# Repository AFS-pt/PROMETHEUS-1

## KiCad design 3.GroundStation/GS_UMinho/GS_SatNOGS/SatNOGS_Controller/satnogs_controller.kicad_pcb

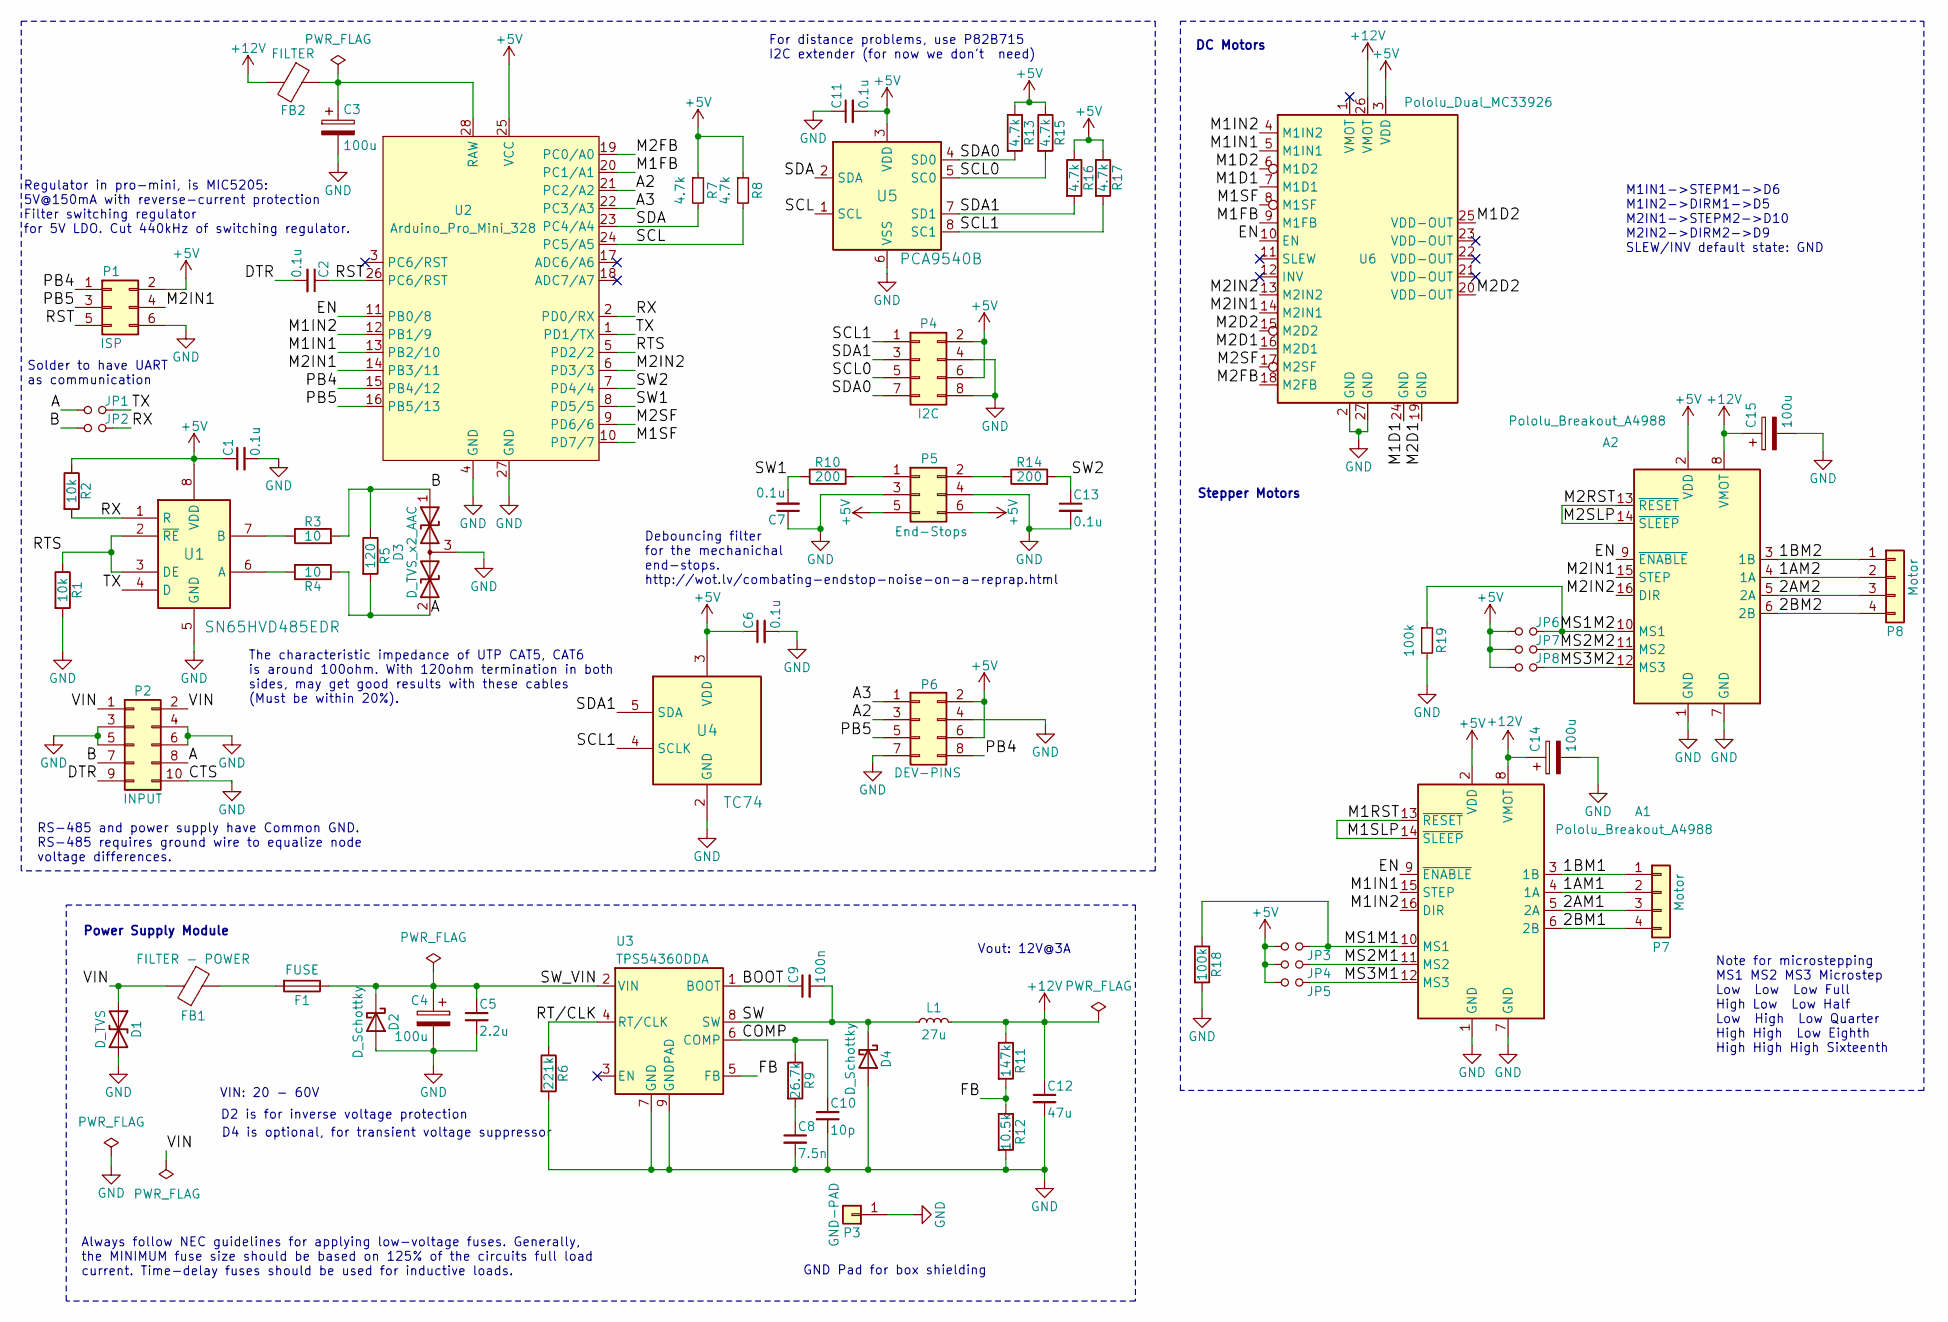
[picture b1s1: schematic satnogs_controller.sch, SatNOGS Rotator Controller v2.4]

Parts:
A1, A2: Pololu_Breakout_A4988; Pololu_Breakout-16_15.2x20.3mm
C1, C2, C6, C7, C11, C13: 0.1u; C_0805_2012Metric_Pad1.15x1.40mm_HandSolder
C3, C14, C15: 100u; CP_Elec_6.3x5.3
C4: 100u; CP_Radial_D10.0mm_P5.00mm
C5: 2.2u; C_1210_3225Metric_Pad1.42x2.65mm_HandSolder
C8: 7.5n; C_0805_2012Metric_Pad1.15x1.40mm_HandSolder
C9: 100n; C_0805_2012Metric_Pad1.15x1.40mm_HandSolder
C10: 10p; C_0805_2012Metric_Pad1.15x1.40mm_HandSolder
C12: 47u; C_1210_3225Metric_Pad1.42x2.65mm_HandSolder
D1: D_TVS; D_SMC_Handsoldering
D2, D4: D_Schottky; D_SMC_Handsoldering
D3: D_TVS_x2_AAC; SOT-23_Handsoldering
F1: FUSE; Fuse_1206_3216Metric_Pad1.42x1.75mm_HandSolder
FB1: FILTER - POWER; R_0805_2012Metric_Pad1.15x1.40mm_HandSolder
FB2: FILTER; R_0805_2012Metric_Pad1.15x1.40mm_HandSolder
JP1, JP2, JP3, JP4, JP5, JP6, JP7, JP8: Jumper_NO_Small; R_0805_2012Metric_Pad1.15x1.40mm_HandSolder
L1: 27u; L_Bourns_SRR1210A
P1: ISP; PinHeader_2x03_P2.54mm_Vertical
P2: INPUT; PinHeader_2x05_P2.54mm_Vertical
P3: GND-PAD; MountingHole_2.2mm_M2_DIN965_Pad
P4: I2C; PinHeader_2x04_P2.54mm_Vertical
P5: End-Stops; PinHeader_2x03_P2.54mm_Vertical
P6: DEV-PINS; PinHeader_2x04_P2.54mm_Vertical
P7, P8: Motor; TerminalBlock_Phoenix_MKDS-1,5-4_1x04_P5.00mm_Horizontal
R1, R2: 10k; R_0805_2012Metric_Pad1.15x1.40mm_HandSolder
R3, R4: 10; R_0805_2012Metric_Pad1.15x1.40mm_HandSolder
R5: 120; R_0805_2012Metric_Pad1.15x1.40mm_HandSolder
R6: 221k; R_0805_2012Metric_Pad1.15x1.40mm_HandSolder
R7, R8, R13, R15, R16, R17: 4.7k; R_0805_2012Metric_Pad1.15x1.40mm_HandSolder
R9: 26.7k; R_0805_2012Metric_Pad1.15x1.40mm_HandSolder
R10, R14: 200; R_0805_2012Metric_Pad1.15x1.40mm_HandSolder
R11: 147k; R_0805_2012Metric_Pad1.15x1.40mm_HandSolder
R12: 10.5k; R_0805_2012Metric_Pad1.15x1.40mm_HandSolder
R18, R19: 100k; R_0805_2012Metric_Pad1.15x1.40mm_HandSolder
U1: SN65HVD485EDR; SOIC-8_3.9x4.9mm_P1.27mm
U2: Arduino_Pro_Mini_328
U3: TPS54360DDA; Texas_HSOP-8-1EP_3.9x4.9mm_P1.27mm_ThermalVias
U4: TC74; SOT-23-5_HandSoldering
U5: PCA9540B; TSSOP-8_3x3mm_P0.65mm
U6: Pololu_Dual_MC33926

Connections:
+5V: A1.2 (VDD), A2.2 (VDD), C1.1, C6.1, C11.2, JP3.2, JP4.2, JP5.2, JP6.1, JP7.1, JP8.1, P1.2, P4.2, P4.6, P5.5, P5.6, P6.2, P6.6, R2.1, R7.1, R8.1, R13.1, R15.1, R16.1, R17.1, U1.8 (VDD), U2.25 (VCC), U4.3 (VDD), U5.3 (VDD), U6.3 (VDD)
+12V: A1.8 (VMOT), A2.8 (VMOT), C12.1, C14.1, C15.1, FB2.2, L1.2, R11.1, U6.26 (VMOT)
/1AM1: A1.4 (1A), P7.2
/1AM2: A2.4 (1A), P8.2
/1BM1: A1.3 (1B), P7.1
/1BM2: A2.3 (1B), P8.1
/2AM1: A1.5 (2A), P7.3
/2AM2: A2.5 (2A), P8.3
/2BM1: A1.6 (2B), P7.4
/2BM2: A2.6 (2B), P8.4
/A: D3.2 (A2), JP1.1, P2.8, R4.1, R5.2
/A2: P6.3, U2.21 (PC2/A2)
/A3: P6.1, U2.22 (PC3/A3)
/B: D3.1 (A1), JP2.1, P2.7, R3.2, R5.1
/BOOT: C9.1, U3.1 (BOOT)
/COMP: C10.1, R9.1, U3.6 (COMP)
/DTR: C2.2, P2.9
/EN: A1.9 (~ENABLE), A2.9 (~ENABLE), U2.11 (PB0/8), U6.10 (EN)
/FB: R11.2, R12.1, U3.5 (FB)
/M1D1: U6.7 (M1D1), U6.24 (GND)
/M1D2: U6.6 (M1D2), U6.25 (VDD-OUT)
/M1FB: U2.20 (PC1/A1), U6.9 (M1FB)
/M1IN1: A1.15 (STEP), U2.13 (PB2/10), U6.5 (M1IN1)
/M1IN2: A1.16 (DIR), U2.12 (PB1/9), U6.4 (M1IN2)
/M1RST: A1.13 (~RESET), A1.14 (~SLEEP)
/M1SF: U2.10 (PD7/7), U6.8 (M1SF)
/M2D1: U6.16 (M2D1), U6.19 (GND)
/M2D2: U6.15 (M2D2), U6.20 (VDD-OUT)
/M2FB: U2.19 (PC0/A0), U6.18 (M2FB)
/M2IN1: A2.15 (STEP), P1.4, U2.14 (PB3/11), U6.14 (M2IN1)
/M2IN2: A2.16 (DIR), U2.6 (PD3/3), U6.13 (M2IN2)
/M2RST: A2.13 (~RESET), A2.14 (~SLEEP)
/M2SF: U2.9 (PD6/6), U6.17 (M2SF)
/MS1M1: A1.10 (MS1), JP3.1, R18.1
/MS1M2: A2.10 (MS1), JP6.2, R19.1
/MS2M1: A1.11 (MS2), JP4.1
/MS2M2: A2.11 (MS2), JP7.2
/MS3M1: A1.12 (MS3), JP5.1
/MS3M2: A2.12 (MS3), JP8.2
/PB4: P1.1, P6.8, U2.15 (PB4/12)
/PB5: P1.3, P6.5, U2.16 (PB5/13)
/RST: C2.1, P1.5, U2.26 (PC6/RST)
/RT/CLK: R6.1, U3.4 (RT/CLK)
/RTS: R1.1, U1.2 (~RE), U1.3 (DE), U2.5 (PD2/2)
/RX: JP2.2, R2.2, U1.1 (R), U2.2 (PD0/RX)
/SCL: R8.2, U2.24 (PC5/A5), U5.1 (SCL)
/SCL0: P4.5, R15.2, U5.5 (SC0)
/SCL1: P4.1, R17.2, U4.4 (SCLK), U5.8 (SC1)
/SDA: R7.2, U2.23 (PC4/A4), U5.2 (SDA)
/SDA0: P4.7, R13.2, U5.4 (SD0)
/SDA1: P4.3, R16.2, U4.5 (SDA), U5.7 (SD1)
/SW: C9.2, D4.1 (K), L1.1, U3.8 (SW)
/SW1: C7.2, R10.1, U2.8 (PD5/5)
/SW2: C13.1, R14.2, U2.7 (PD4/4)
/SW_VIN: C4.1, C5.1, D2.1 (K), F1.1, U3.2 (VIN)
/TX: JP1.2, U1.4 (D), U2.1 (PD1/TX)
/VIN: D1.1 (A1), FB1.2, P2.1, P2.2
GND: A1.1 (GND), A1.7 (GND), A2.1 (GND), A2.7 (GND), C1.2, C3.2, C4.2, C5.2, C6.2, C7.1, C8.2, C10.2, C11.1, C12.2, C13.2, C14.2, C15.2, D1.2 (A2), D2.2 (A), D3.3 (common), D4.2 (A), P1.6, P2.3, P2.4, P2.5, P2.6, P2.10, P3.1, P4.4, P4.8, P5.3, P5.4, P6.4, P6.7, R1.2, R6.2, R12.2, R18.2, R19.2, U1.5 (GND), U2.4 (GND), U2.27 (GND), U3.7 (GND), U3.9 (GNDPAD), U4.2 (GND), U5.6 (VSS), U6.2 (GND), U6.27 (GND)
unnamed: C3.1, FB2.1, U2.28 (RAW)
unnamed: C8.1, R9.2
unnamed: F1.2, FB1.1
unnamed: P5.1, R10.2
unnamed: P5.2, R14.1
unnamed: R3.1, U1.7 (B)
unnamed: R4.2, U1.6 (A)

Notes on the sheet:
M1IN1->STEPM1->D6 M1IN2->DIRM1->D5 M2IN1->STEPM2->D10 M2IN2->DIRM2->D9 SLEW/INV default state: GND
DC Motors
Stepper Motors
Regulator in pro-mini, is MIC5205: 5V@150mA with reverse-current protection Filter switching regulator for 5V LDO. Cut 440kHz of switching regulator.
Note for microstepping MS1 MS2 MS3 Microstep Low Low Low Full High Low Low Half Low High Low Quarter High High Low Eighth High High High Sixteenth
Power Supply Module
Solder to have UART as communication
Vout: 12V@3A
VIN: 20 - 60V
Debouncing filter for the mechanichal end-stops. http://wot.lv/combating-endstop-noise-on-a-reprap.html
For distance problems, use P82B715 I2C extender (for now we don't need)
D2 is for inverse voltage protection
Always follow NEC guidelines for applying low-voltage fuses. Generally, the MINIMUM fuse size should be based on 125% of the circuits full load current. Time-delay fuses should be used for inductive loads.
GND Pad for box shielding
The characteristic impedance of UTP CAT5, CAT6 is around 100ohm. With 120ohm termination in both sides, may get good results with these cables (Must be within 20%).
RS-485 and power supply have Common GND. RS-485 requires ground wire to equalize node voltage differences.
D4 is optional, for transient voltage suppressor

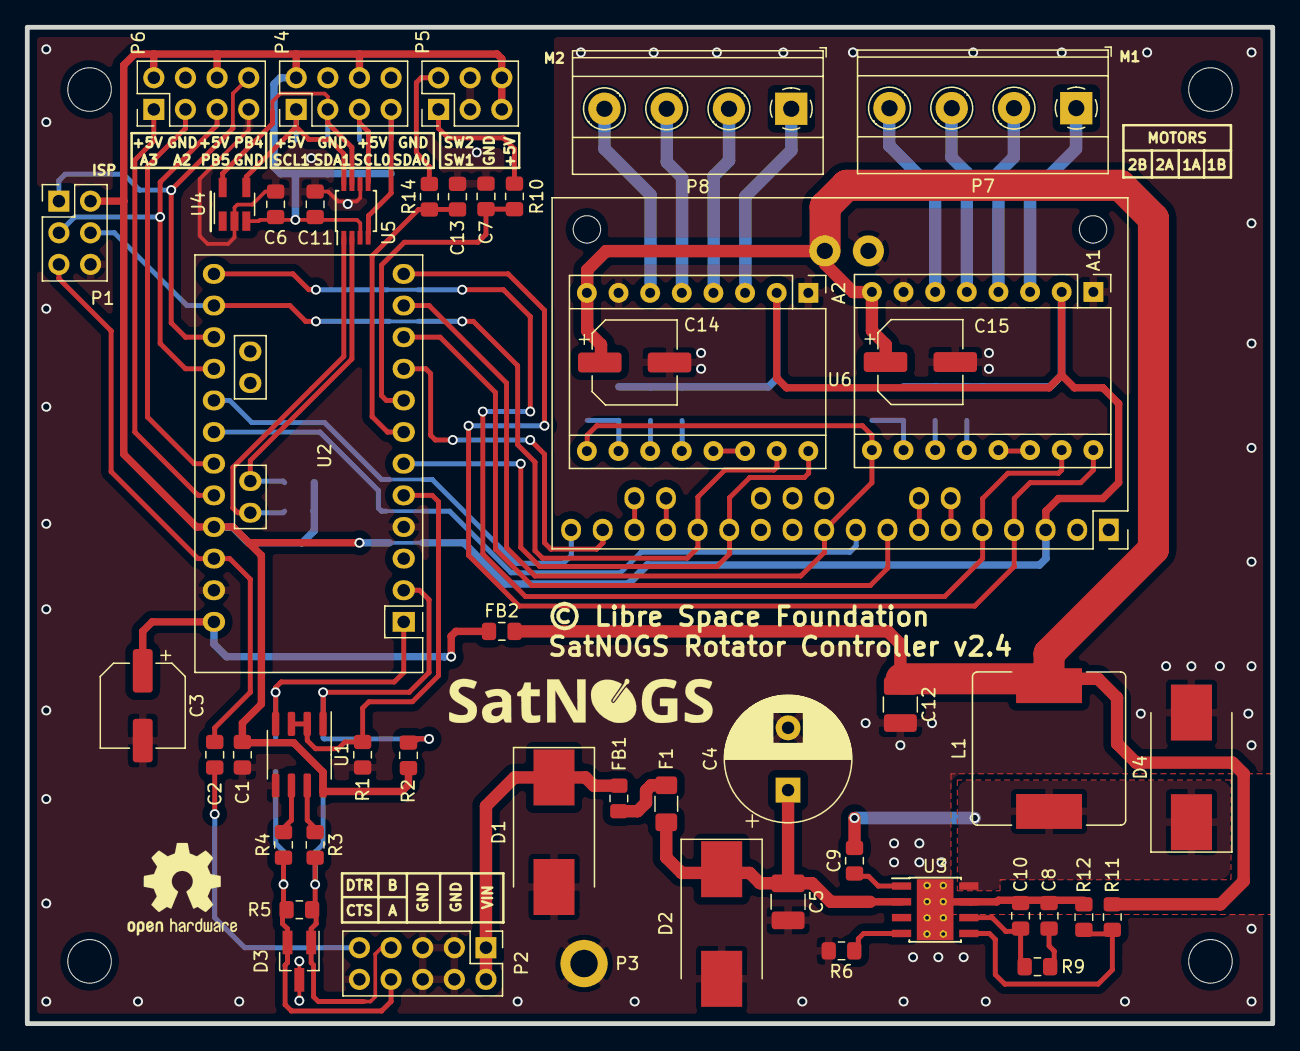
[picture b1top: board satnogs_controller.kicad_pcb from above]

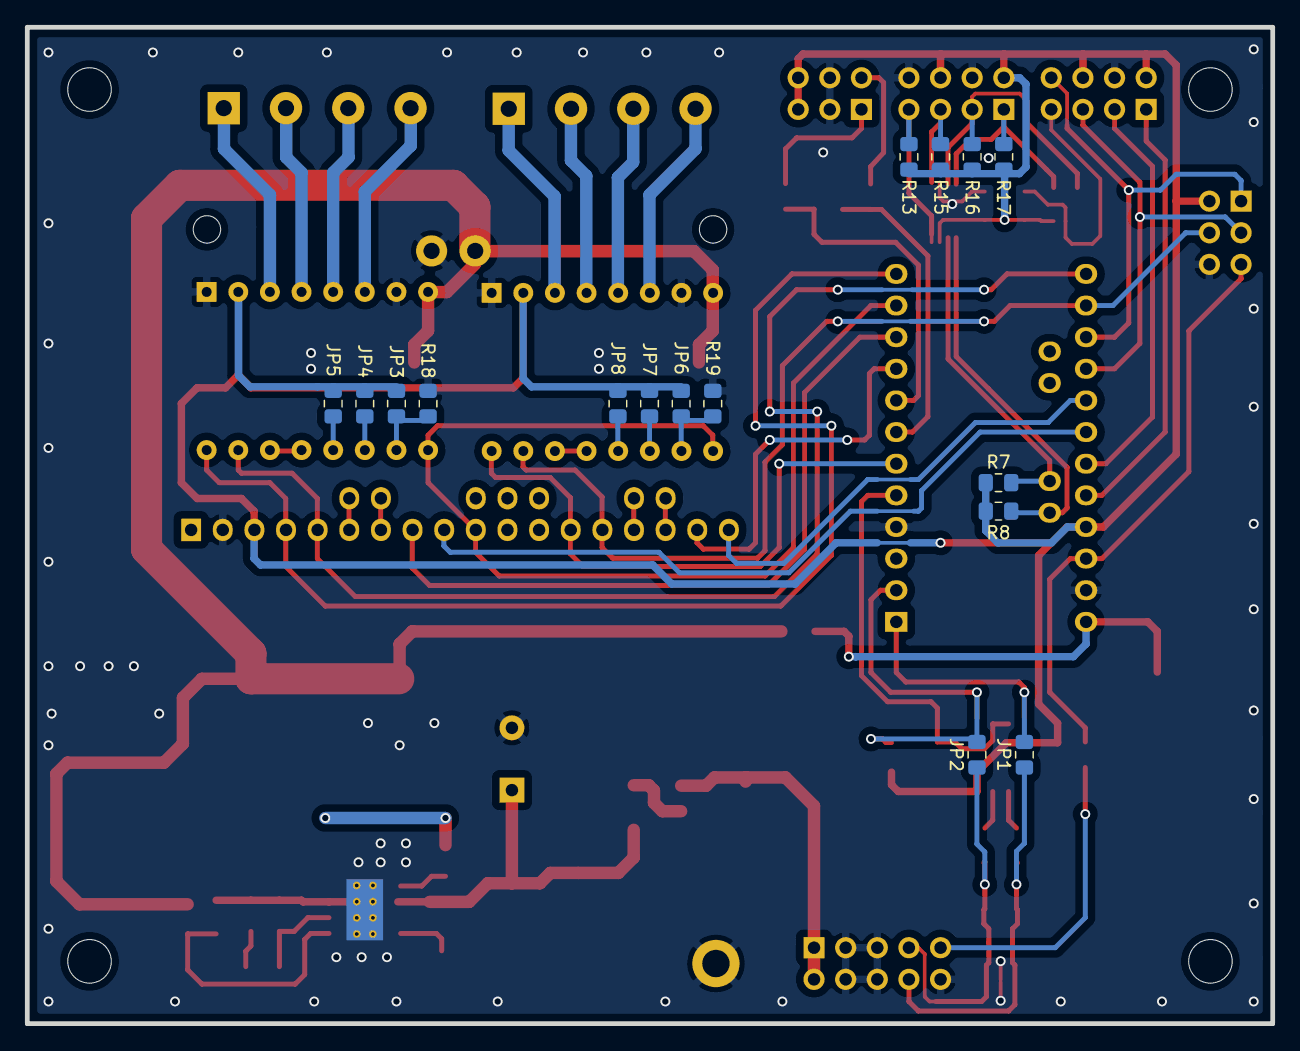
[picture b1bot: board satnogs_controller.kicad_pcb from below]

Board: 2 copper layers, 100.0 x 80.0 mm, 67 parts (16 on the bottom side), 65 nets.

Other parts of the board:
Board: EuroBoard_halb_Type-I_100mmX80mm_holes

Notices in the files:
3.GroundStation/GS_UMinho/GS_SatNOGS/SatNOGS_Controller/satnogs_controller.kicad_pcb:
© Libre Space Foundation
